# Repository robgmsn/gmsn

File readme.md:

Welcome to GMSN!

Your complete portal to building a DIY Open Source Synthesiser.

On the main [GMSN! Website](https://gmsn.co.uk/) you will find all the designs, PCBs and Panels, together with step by step instructions and parts lists.

Supporters of GMSN! can access build docs and support via the [GMSN! Forum](https://forum.gmsn.co.uk/). Please buy PCBs and Panels direct from the website to create a forum acccount.

This Github Repo contains the code for the digital modules. All of which are based on the ATMEGA328 microprocessor. This enable us to leverage the Arduino IDE and libraries, which speeds up code development and deployment.

You can also view the Eagle Schematics and Board files on [CADLAB.io](https://cadlab.io/project/24118). This displays component locations and also tracks changes between versions.

There's also the [GMSN! Youtube Channel](https://www.youtube.com/channel/UCwt7YFF0vUFElzAl-tT9rXA) for loads of great tips on getting started.

All designs are released under cc-by 4.0 license.

* SA - Share & Adapt.
* BY - Credit where credit is due.
* For any purpose including Commercial and Group Buys.
* No pressure to share design files

Time to build synths!

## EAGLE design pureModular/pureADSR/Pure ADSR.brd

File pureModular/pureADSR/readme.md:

DESIGN STATUS: Awaiting Testing - Ready for beta testing

ADSR Updated to V2.2 14/4/21

Library updated to include 3D models.
Traces rerouted.
DAC output filter remodelled.
Power replaced so 5V comes from power supply rather than 12V, in line with low noise techniques.

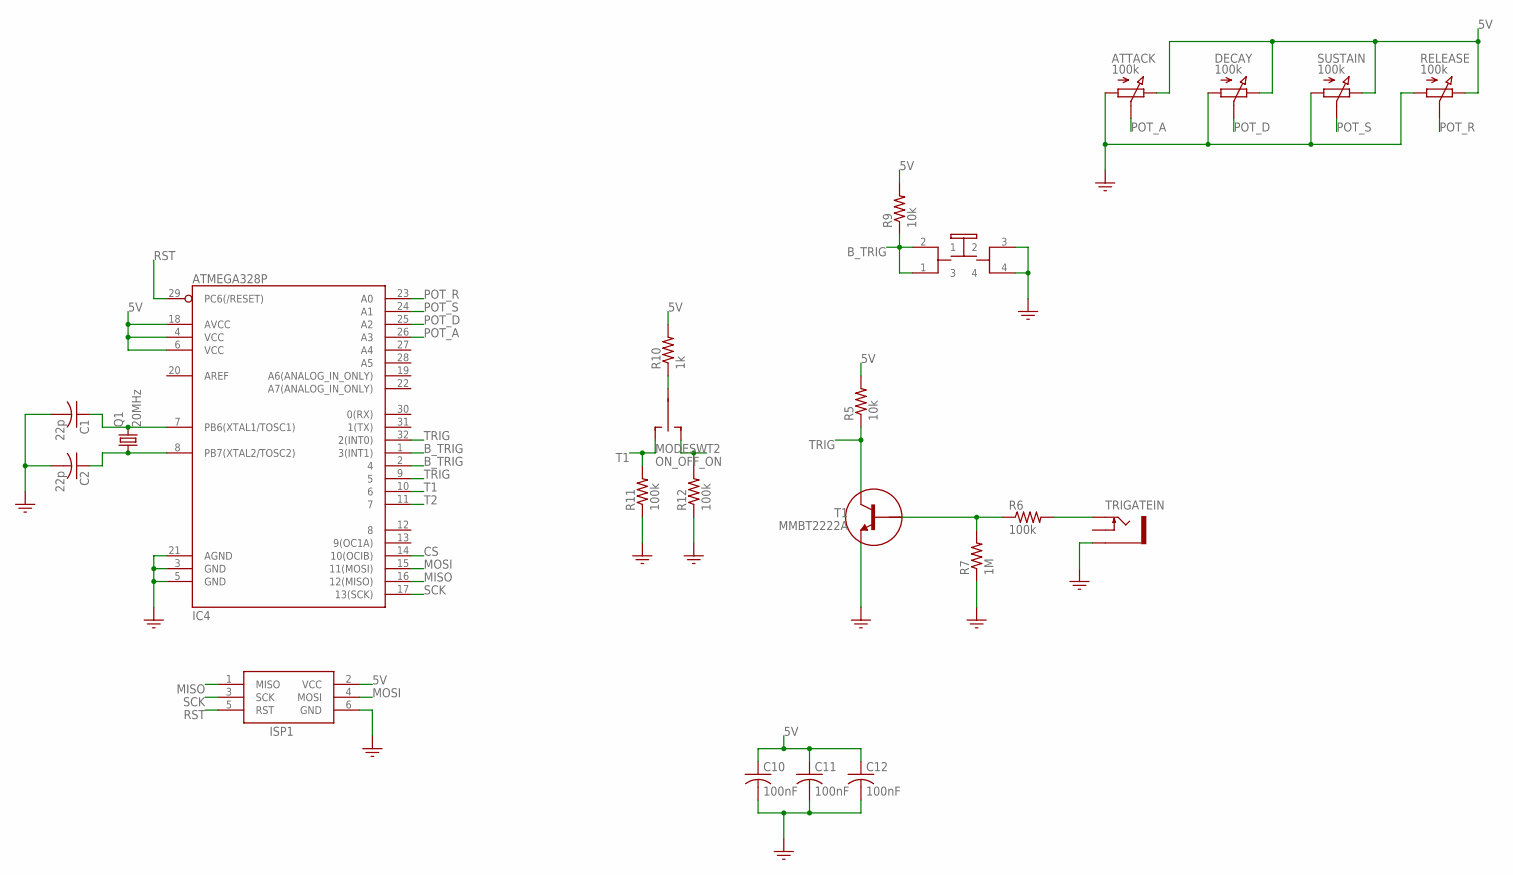
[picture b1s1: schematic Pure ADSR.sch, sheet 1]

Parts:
ATTACK: 100k; POTENTIOMETER_9MM
C1, C2: 22p; C0805
C10, C11, C12: 100nF; C0805
DECAY: 100k; POTENTIOMETER_9MM
IC4: ATMEGA328P; TQFP32-08
ISP1: HEADER2X3-6; AVRISP
MODESW: ON_OFF_ON; TOGGLE_SW
Q1: 20MHz; HC49UP
R5, R9: 10k; R0805
R6, R11, R12: 100k; R0805
R7: 1M; R0805
R10: 1k; R0805
RELEASE: 100k; POTENTIOMETER_9MM
SUSTAIN: 100k; POTENTIOMETER_9MM
T1: MMBT2222A; SOT23
TRIGATEIN: SOCKET_MONO_3.5MMPJ301M-12; PJ301M-12
TRIGGER: PB6149L-5; PB6149L

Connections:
5V: ATTACK.P$3 (3), C10.1, C11.1, C12.1, DECAY.P$3 (3), IC4.4 (VCC), IC4.6 (VCC), IC4.18 (AVCC), ISP1.2 (VCC), R5.2, R9.2, R10.2, RELEASE.P$3 (3), SUSTAIN.P$3 (3); also elsewhere on the board
B_TRIG: IC4.1 (3(INT1)), IC4.2 (4), R9.1, TRIGGER.1 (3), TRIGGER.2 (1)
CS: IC4.14 (10(OCIB)); also elsewhere on the board
GND: ATTACK.P$1 (1), C1.2, C2.2, C10.2, C11.2, C12.2, DECAY.P$1 (1), IC4.3 (GND), IC4.5 (GND), IC4.21 (AGND), ISP1.6 (GND), R7.1, R11.1, R12.1, RELEASE.P$1 (1), SUSTAIN.P$1 (1), T1.2 (E), TRIGATEIN.GND (SLEEVE), TRIGGER.3 (2), TRIGGER.4; also elsewhere on the board
MISO: IC4.16 (12(MISO)), ISP1.1 (MISO)
MOSI: IC4.15 (11(MOSI)), ISP1.4 (MOSI); also elsewhere on the board
unnamed: C1.1, IC4.7 (PB6(XTAL1/TOSC1)), Q1.2
unnamed: C2.1, IC4.8 (PB7(XTAL2/TOSC2)), Q1.1
unnamed: MODESW.2, R10.1
unnamed: R6.1, R7.2, T1.1 (B)
unnamed: R6.2, TRIGATEIN.TIP
POT_A: ATTACK.P$2 (2), IC4.26 (A3)
POT_D: DECAY.P$2 (2), IC4.25 (A2)
POT_R: IC4.23 (A0), RELEASE.P$2 (2)
POT_S: IC4.24 (A1), SUSTAIN.P$2 (2)
RST: IC4.29 (PC6(/RESET)), ISP1.5 (RST)
SCK: IC4.17 (13(SCK)), ISP1.3 (SCK); also elsewhere on the board
T1: IC4.10 (6), MODESW.3 (S), R11.2
T2: IC4.11 (7), MODESW.1 (O), R12.2
TRIG: IC4.9 (5), IC4.32 (2(INT0)), R5.1, T1.3 (C)

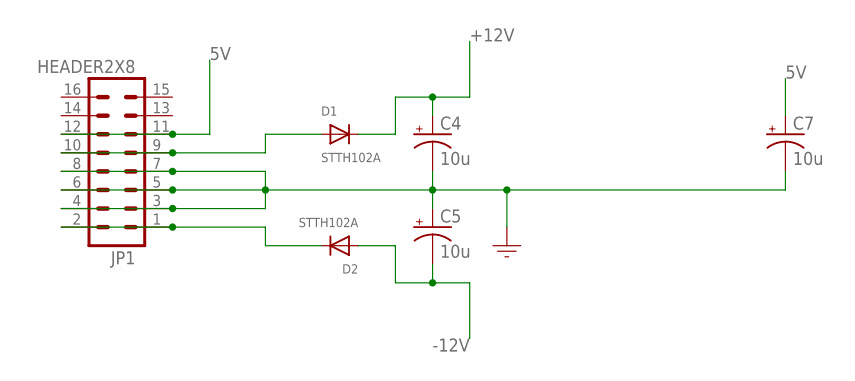
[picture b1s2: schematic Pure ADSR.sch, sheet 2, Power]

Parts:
C4, C5, C7: 10u; 153CLV-0505
D1, D2: STTH102A; SMADIODE
JP1: HEADER2X8; POWER_SHROUDED

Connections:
5V: C7.+, JP1.11, JP1.12; also elsewhere on the board
+12V: C4.+, D1.C; also elsewhere on the board
-12V: C5.-, D2.A; also elsewhere on the board
GND: C4.-, C5.+, C7.-, JP1.3, JP1.4, JP1.5, JP1.6, JP1.7, JP1.8; also elsewhere on the board
unnamed: D2.C, JP1.1, JP1.2
unnamed: D1.A, JP1.9, JP1.10

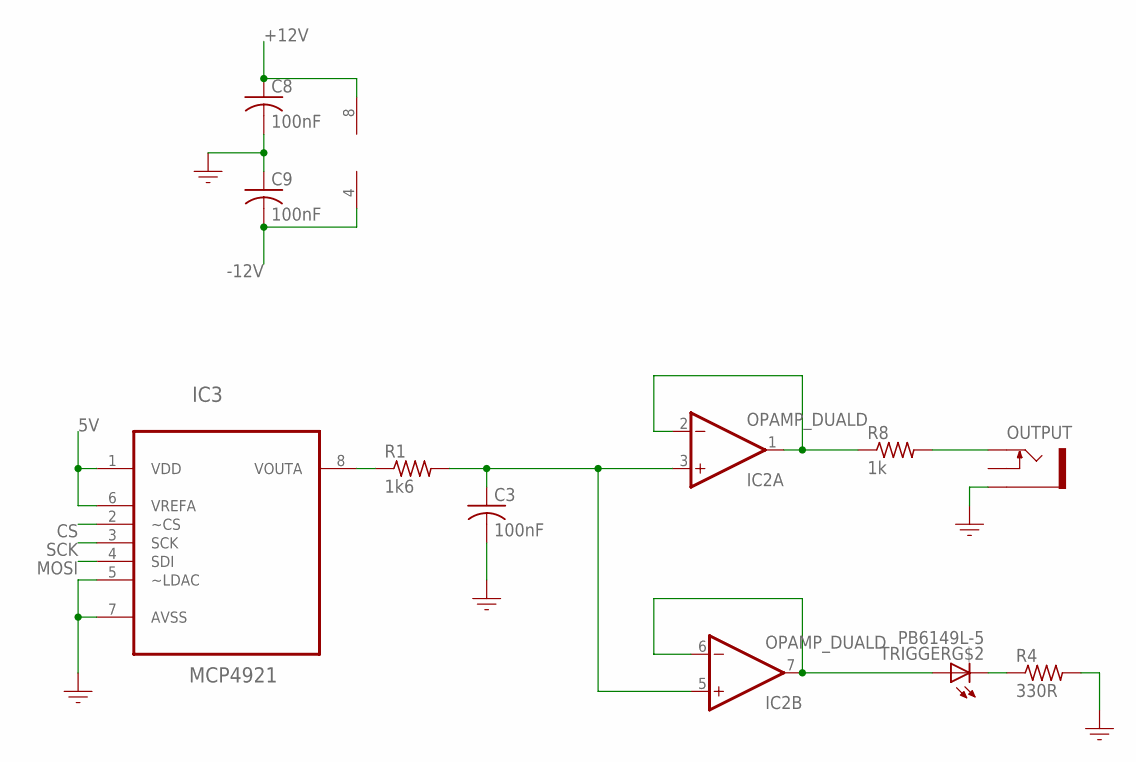
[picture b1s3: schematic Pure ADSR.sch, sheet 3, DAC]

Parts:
C3, C8, C9: 100nF; C0805
IC2: OPAMP_DUALD; SO08
IC3: MCP4921; SOIC8
OUTPUT: SOCKET_MONO_3.5MMPJ301M-12; PJ301M-12
R1: 1k6; R0805
R4: 330R; R0805
R8: 1k; R0805
TRIGGER: PB6149L-5; PB6149L

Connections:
5V: IC3.1 (VDD), IC3.6 (VREFA); also elsewhere on the board
+12V: C8.1, IC2.8 (V+); also elsewhere on the board
-12V: C9.2, IC2.4 (V-); also elsewhere on the board
CS: IC3.2 (~CS); also elsewhere on the board
GND: C3.2, C8.2, C9.1, IC3.5 (~LDAC), IC3.7 (AVSS), OUTPUT.GND (SLEEVE), R4.2; also elsewhere on the board
MOSI: IC3.4 (SDI); also elsewhere on the board
unnamed: IC3.8 (VOUTA), R1.1
unnamed: C3.1, IC2.3 (+IN), IC2.5 (+IN), R1.2
unnamed: IC2.1 (OUT), IC2.2 (-IN), R8.1
unnamed: IC2.6 (-IN), IC2.7 (OUT), TRIGGER.A
unnamed: R4.1, TRIGGER.K (C)
unnamed: OUTPUT.TIP, R8.2
SCK: IC3.3 (SCK); also elsewhere on the board

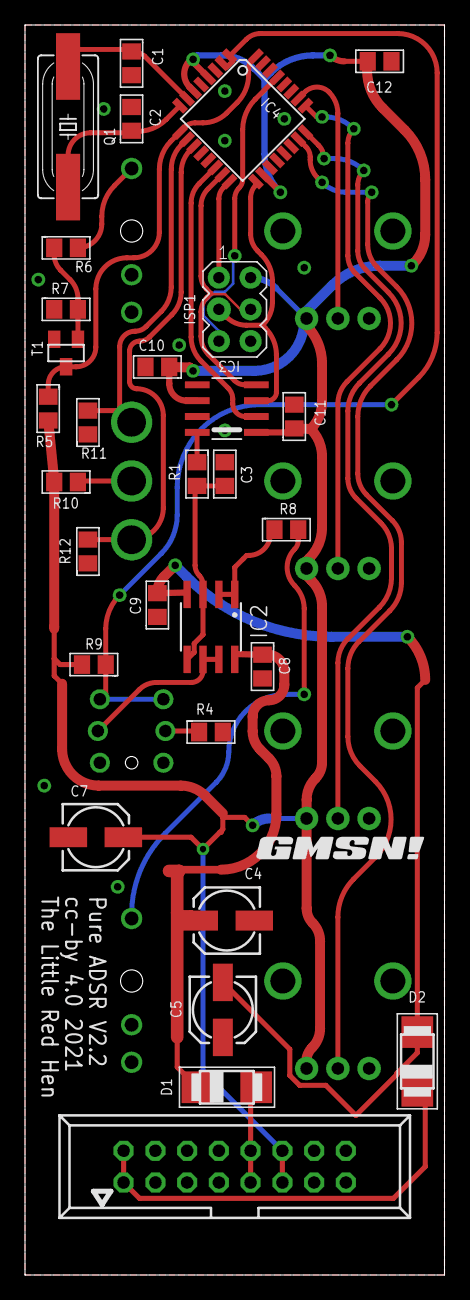
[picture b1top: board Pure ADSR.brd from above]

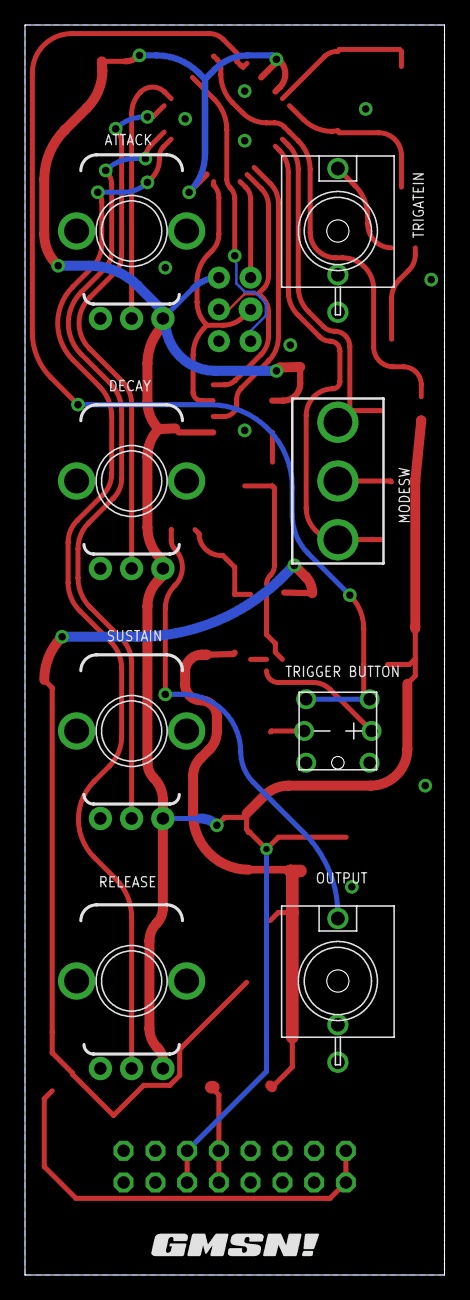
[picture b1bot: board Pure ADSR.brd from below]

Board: 2 copper layers, 33.6 x 100.0 mm, 40 parts (9 on the bottom side), 30 nets.

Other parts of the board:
U$1, U$2: GMSN!_LOGO

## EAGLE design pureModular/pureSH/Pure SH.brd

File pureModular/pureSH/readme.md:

DESIGN STATUS: Awaiting Testing - Ready for beta testing

S&H Updated to V1.5 14/4/21

Library updated to include 3D models.
Traces rerouted.

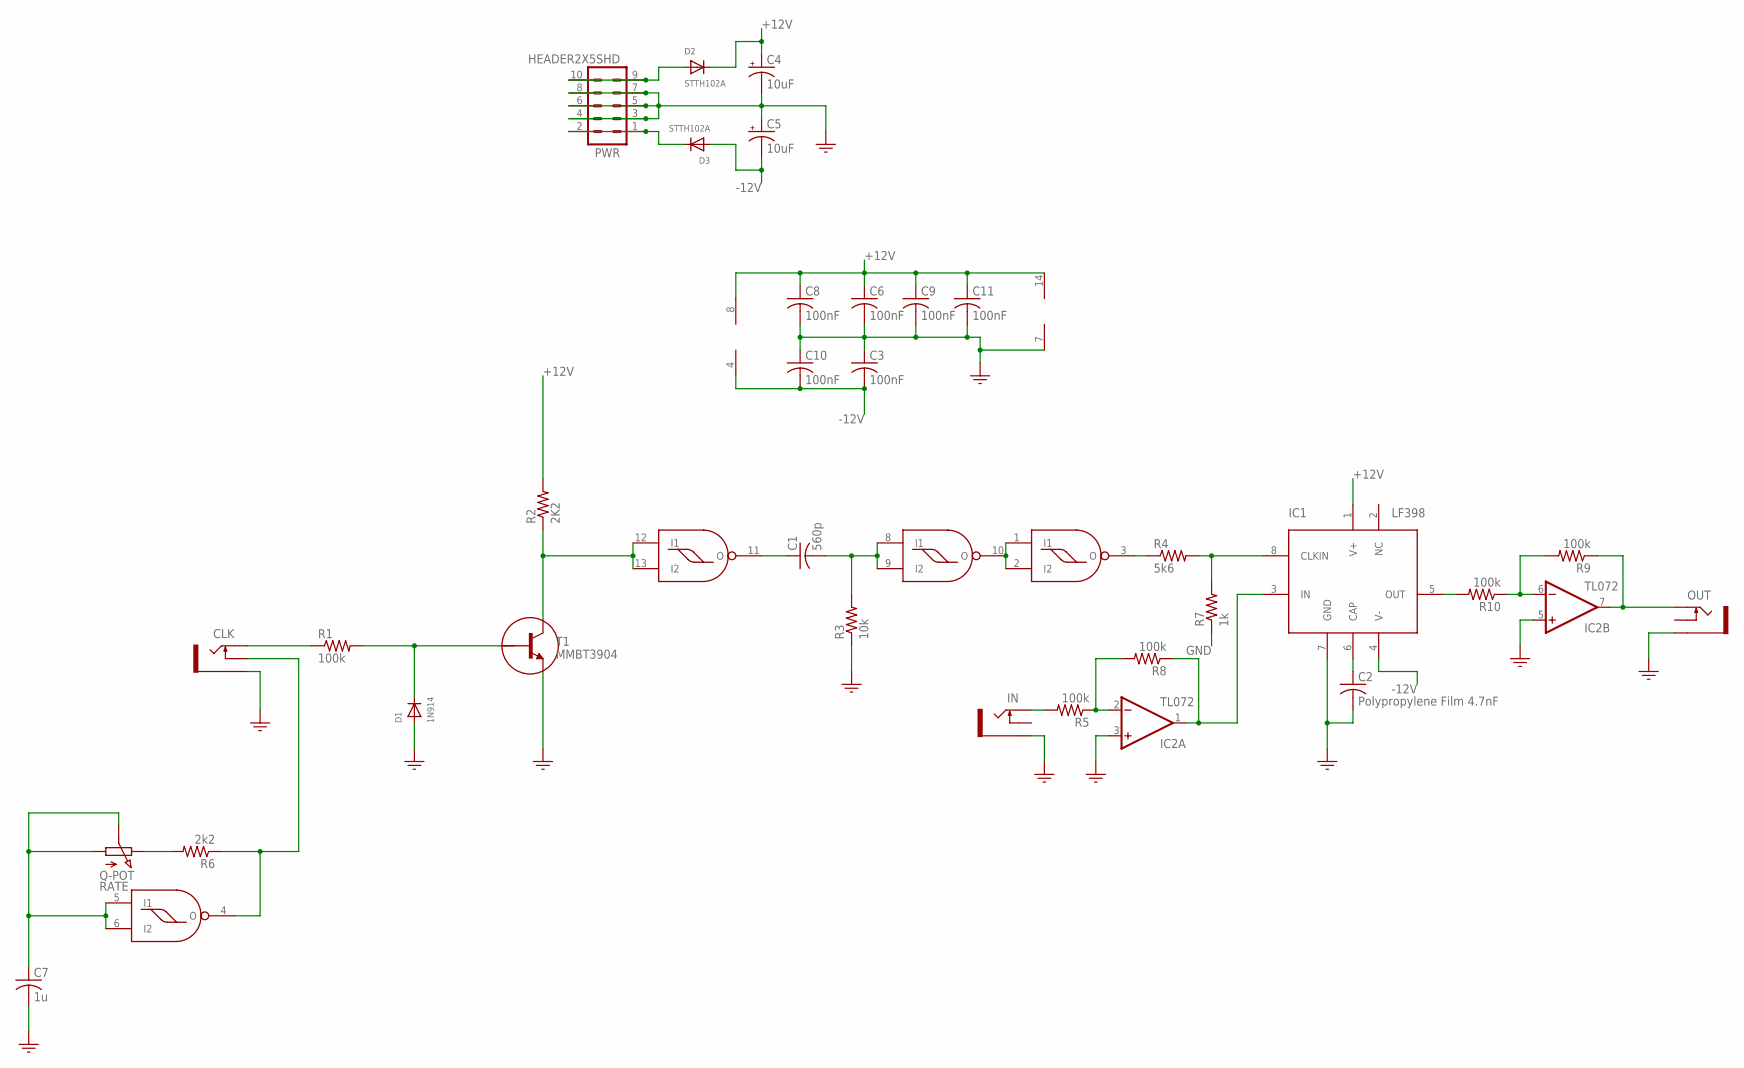
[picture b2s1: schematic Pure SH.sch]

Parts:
C1: 560p; C0805
C2: Polypropylene Film 4.7nF; C050-045X075
C3, C6, C8, C9, C10, C11: 100nF; C0805
C4, C5: 10uF; 153CLV-0505
C7: 1u; C0805
CLK: PJ301M-12
D1: 1N914; DO-41
D2, D3: STTH102A; SMADIODE
IC1: LF398; SOIC--8
IC2: TL072; SO08
IC3: cd4093; SOIC14
IN: PJ301M-12
OUT: PJ301M-12
PWR: HEADER2X5SHD; 2X5-SHROUDED
R1, R5, R8, R9, R10: 100k; R0805
R2: 2K2; R0805
R3: 10k; R0805
R4: 5k6; R0805
R6: 2k2; R0805
R7: 1k; R0805
RATE: Q-POT; POTENTIOMETER_9MM
T1: MMBT3904; SOT23

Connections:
+12V: C4.+, C6.1, C8.1, C9.1, C11.1, D2.C, IC1.1 (V+), IC2.8 (V+), IC3.14 (V+), R2.2
-12V: C3.2, C5.-, C10.2, D3.A, IC1.4 (V-), IC2.4 (V-)
GND: C2.2, C3.1, C4.-, C5.+, C6.2, C7.2, C8.2, C9.2, C10.1, C11.2, CLK.GND (SLEEVE), D1.A, IC1.7 (GND), IC2.3 (+IN), IC2.5 (+IN), IC3.7 (V-), IN.GND (SLEEVE), OUT.GND (SLEEVE), PWR.3, PWR.4, PWR.5, PWR.6, PWR.7, PWR.8, R3.1, R7.1, T1.2 (E)
unnamed: CLK.TIP, R1.1
unnamed: D1.C, R1.2, T1.1 (B)
unnamed: C1.1, IC3.11 (O)
unnamed: IC3.12 (I1), IC3.13 (I2), R2.1, T1.3 (C)
unnamed: IC3.1 (I1), IC3.2 (I2), IC3.10 (O)
unnamed: IC1.8 (CLKIN), R4.2, R7.2
unnamed: C1.2, IC3.8 (I1), IC3.9 (I2), R3.2
unnamed: IC3.3 (O), R4.1
unnamed: C2.1, IC1.6 (CAP)
unnamed: IN.TIP, R5.2
unnamed: IC2.2 (-IN), R5.1, R8.2
unnamed: R6.2, RATE.P$3 (3)
unnamed: C7.1, IC3.5 (I1), IC3.6 (I2), RATE.P$1 (1), RATE.P$2 (2)
unnamed: CLK.NORM (SWITCH), IC3.4 (O), R6.1
unnamed: IC1.3 (IN), IC2.1 (OUT), R8.1
unnamed: IC1.5 (OUT), R10.2
unnamed: IC2.6 (-IN), R9.2, R10.1
unnamed: IC2.7 (OUT), OUT.TIP, R9.1
unnamed: D2.A, PWR.9, PWR.10
unnamed: D3.C, PWR.1, PWR.2

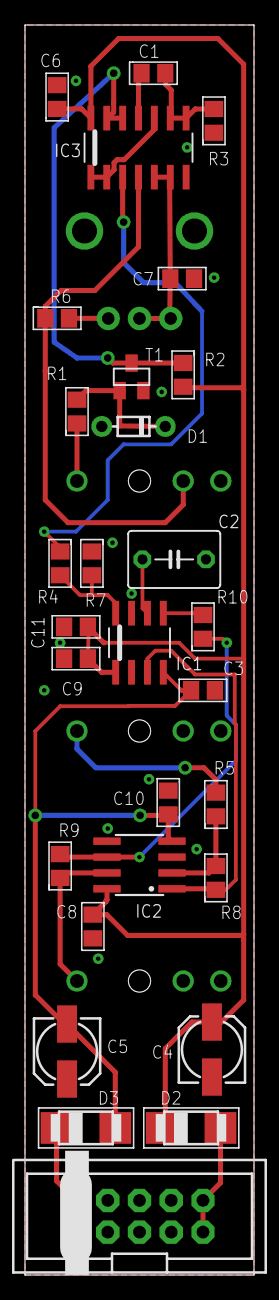
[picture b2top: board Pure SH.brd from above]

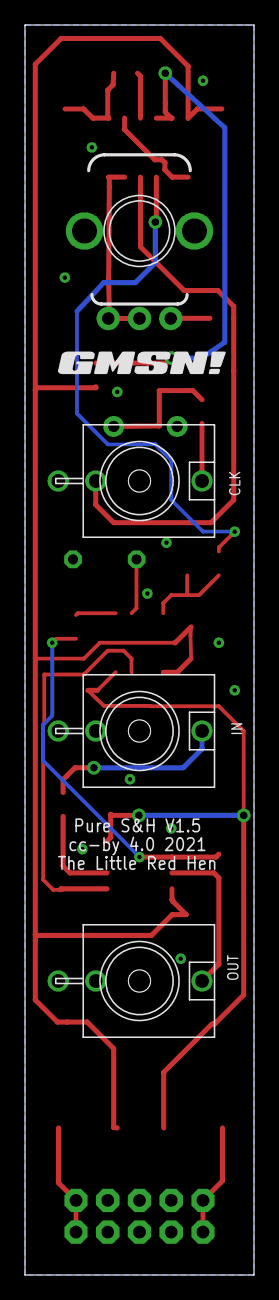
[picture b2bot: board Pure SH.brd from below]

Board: 2 copper layers, 18.3 x 100.0 mm, 34 parts (5 on the bottom side), 23 nets.

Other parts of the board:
U$3: GMSN!_LOGO

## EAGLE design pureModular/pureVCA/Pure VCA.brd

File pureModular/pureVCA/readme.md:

DESIGN STATUS: Awaiting Testing - Ready for beta testing

VCA Updated to V2.3 14/4/21

Library updated to include 3D models.
Traces rerouted.
Weird shorted cap removed. WTF?

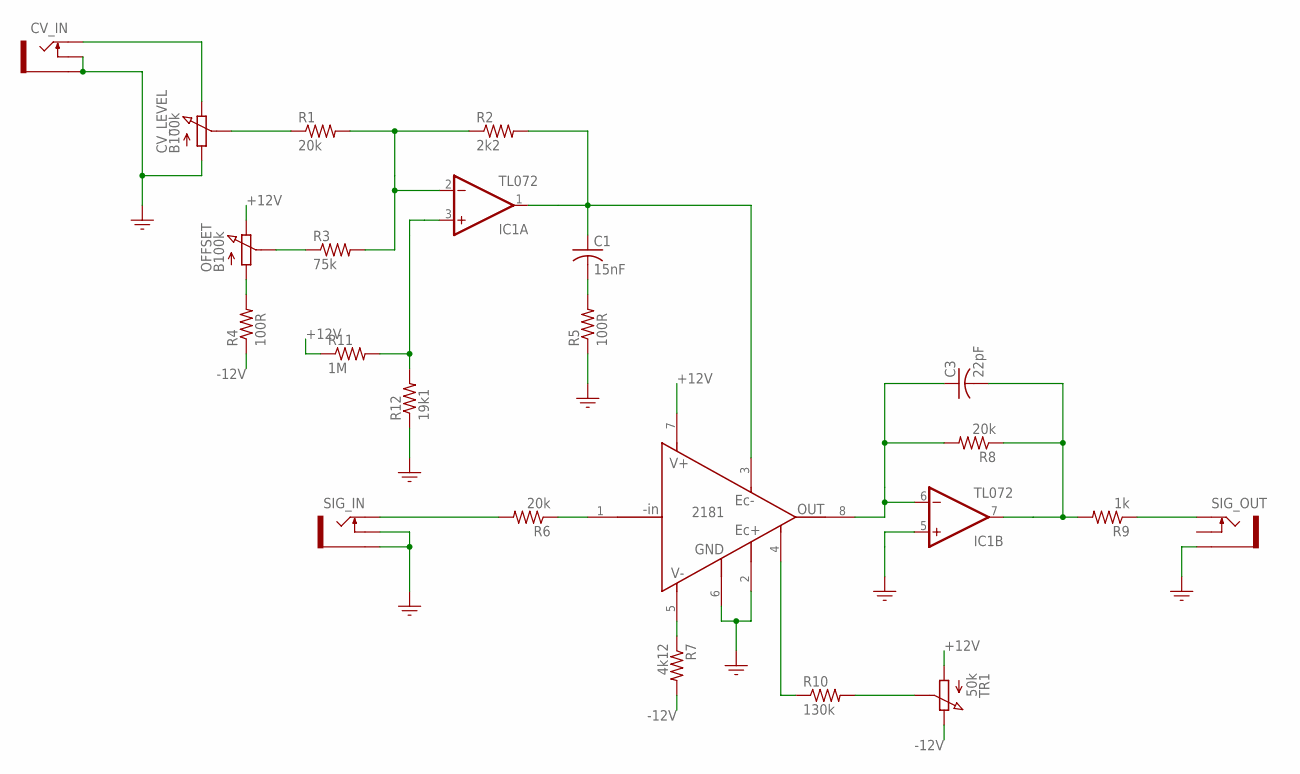
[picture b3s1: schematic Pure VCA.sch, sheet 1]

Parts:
C1: 15nF; C0805
C3: 22pF; C0805
CV_IN: PJ301M-12
CV_LEVEL: B100k; POT_9MM_GREEN_KNOB
IC1: TL072; SO08
IC2: THAT2181; SOIC--8
OFFSET: B100k; POT_9MM_BLUE_KNOB
R1, R6, R8: 20k; R0805
R2: 2k2; R0805
R3: 75k; R0805
R4, R5: 100R; R0805
R7: 4k12; R0805
R9: 1k; R0805
R10: 130k; R0805
R11: 1M; R0805
R12: 19k1; R0805
SIG_IN: PJ301M-12
SIG_OUT: PJ301M-12
TR1: 50k; TRIMMER_TH

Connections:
+12V: IC2.7 (V+), OFFSET.P$3 (3), R11.1, TR1.1; also elsewhere on the board
-12V: R4.1, R7.2, TR1.3; also elsewhere on the board
GND: CV_IN.GND (SLEEVE), CV_IN.NORM (SWITCH), CV_LEVEL.P$1 (1), IC1.5 (+IN), IC2.2 (EC+), IC2.6 (GND), R5.1, R12.1, SIG_IN.GND (SLEEVE), SIG_IN.NORM (SWITCH), SIG_OUT.GND (SLEEVE); also elsewhere on the board
unnamed: CV_IN.TIP, CV_LEVEL.P$3 (3)
unnamed: IC1.2 (-IN), R1.2, R2.1, R3.2
unnamed: CV_LEVEL.P$2 (2), R1.1
unnamed: OFFSET.P$1 (1), R4.2
unnamed: C1.1, IC1.1 (OUT), IC2.3 (EC-), R2.2
unnamed: OFFSET.P$2 (2), R3.1
unnamed: C1.2, R5.2
unnamed: R9.1, SIG_OUT.TIP
unnamed: IC2.1 (-IN), R6.1
unnamed: R6.2, SIG_IN.TIP
unnamed: IC2.5 (V-), R7.1
unnamed: IC1.3 (+IN), R11.2, R12.2
unnamed: C3.1, IC1.6 (-IN), IC2.8 (OUT), R8.2
unnamed: C3.2, IC1.7 (OUT), R8.1, R9.2
unnamed: IC2.4 (SYM), R10.1
unnamed: R10.2, TR1.2

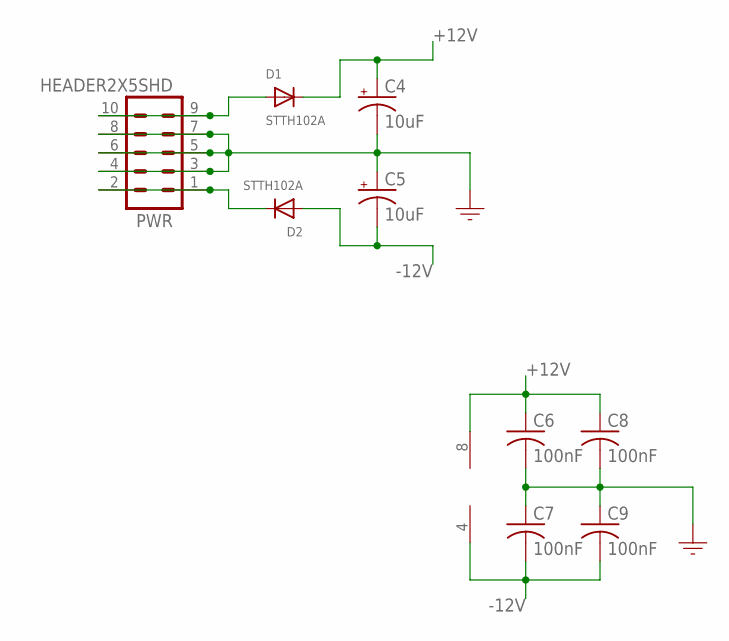
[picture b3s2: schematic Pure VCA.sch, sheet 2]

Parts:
C4, C5: 10uF; 153CLV-0505
C6, C7, C8, C9: 100nF; C0805
D1, D2: STTH102A; SMADIODE
IC1: TL072; SO08
PWR: HEADER2X5SHD; 2X5-SHROUDED

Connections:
+12V: C4.+, C6.1, C8.1, D1.C, IC1.8 (V+); also elsewhere on the board
-12V: C5.-, C7.2, C9.2, D2.A, IC1.4 (V-); also elsewhere on the board
GND: C4.-, C5.+, C6.2, C7.1, C8.2, C9.1, PWR.3, PWR.4, PWR.5, PWR.6, PWR.7, PWR.8; also elsewhere on the board
unnamed: D1.A, PWR.9, PWR.10
unnamed: D2.C, PWR.1, PWR.2

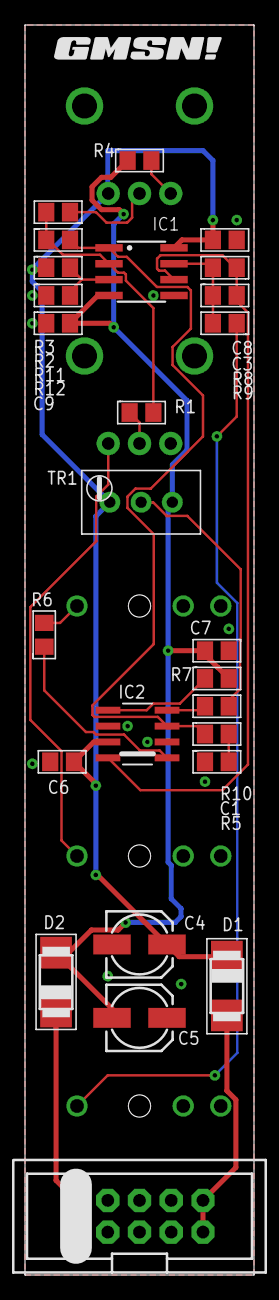
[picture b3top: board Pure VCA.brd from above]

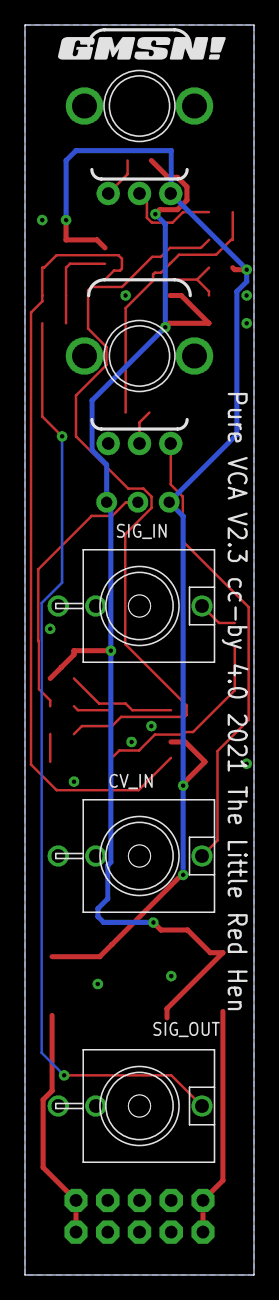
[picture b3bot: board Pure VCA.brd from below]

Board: 2 copper layers, 18.3 x 100.0 mm, 33 parts (6 on the bottom side), 21 nets.

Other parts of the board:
U$1, U$2: GMSN!_LOGO

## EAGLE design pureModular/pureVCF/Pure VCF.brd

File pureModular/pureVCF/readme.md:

DESIGN STATUS: Awaiting Testing - Not for public consumption.

VCF Updated to V2.5 14/04/21

Library updated to 3D models.
Changed the CV mixer from Average to Sum and added inverter stage to retain consistency.
Some resistor values reduced to 10K, inline with low noise techniques.
Rerouted and reduced some traces.

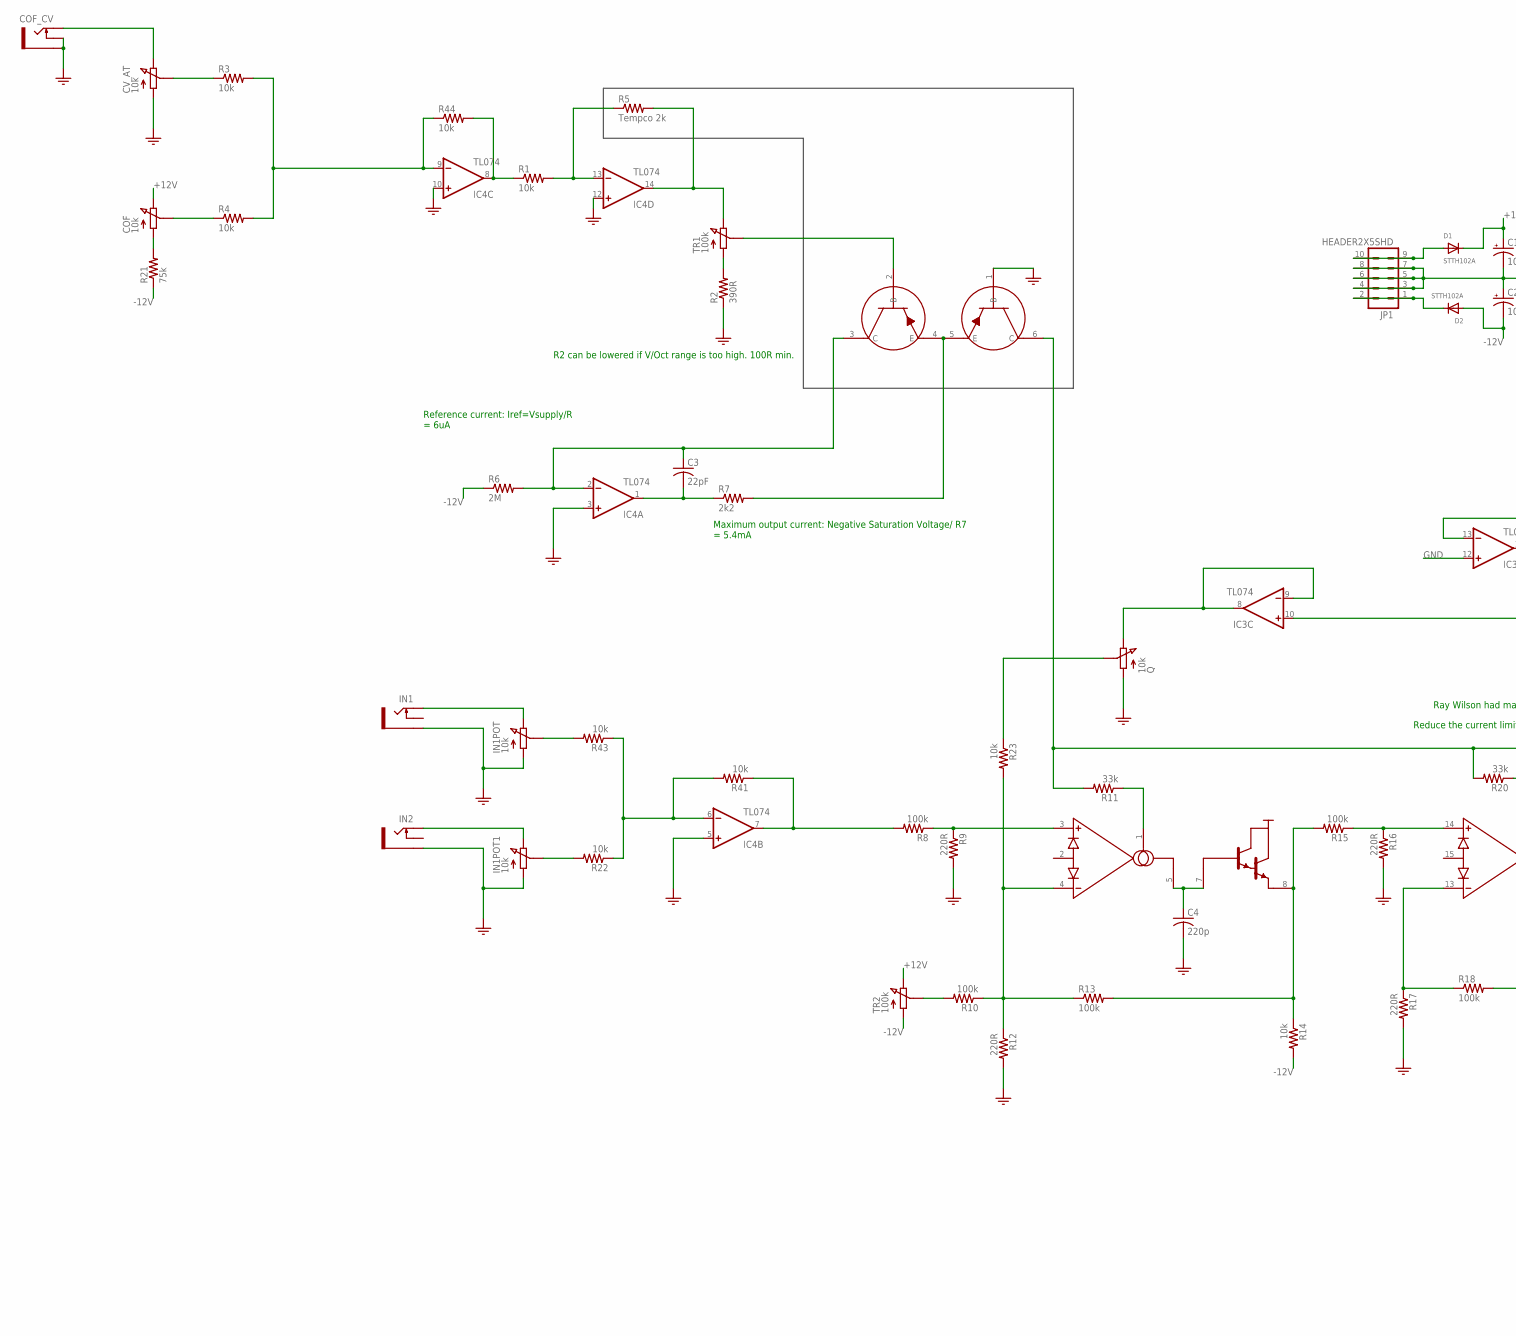
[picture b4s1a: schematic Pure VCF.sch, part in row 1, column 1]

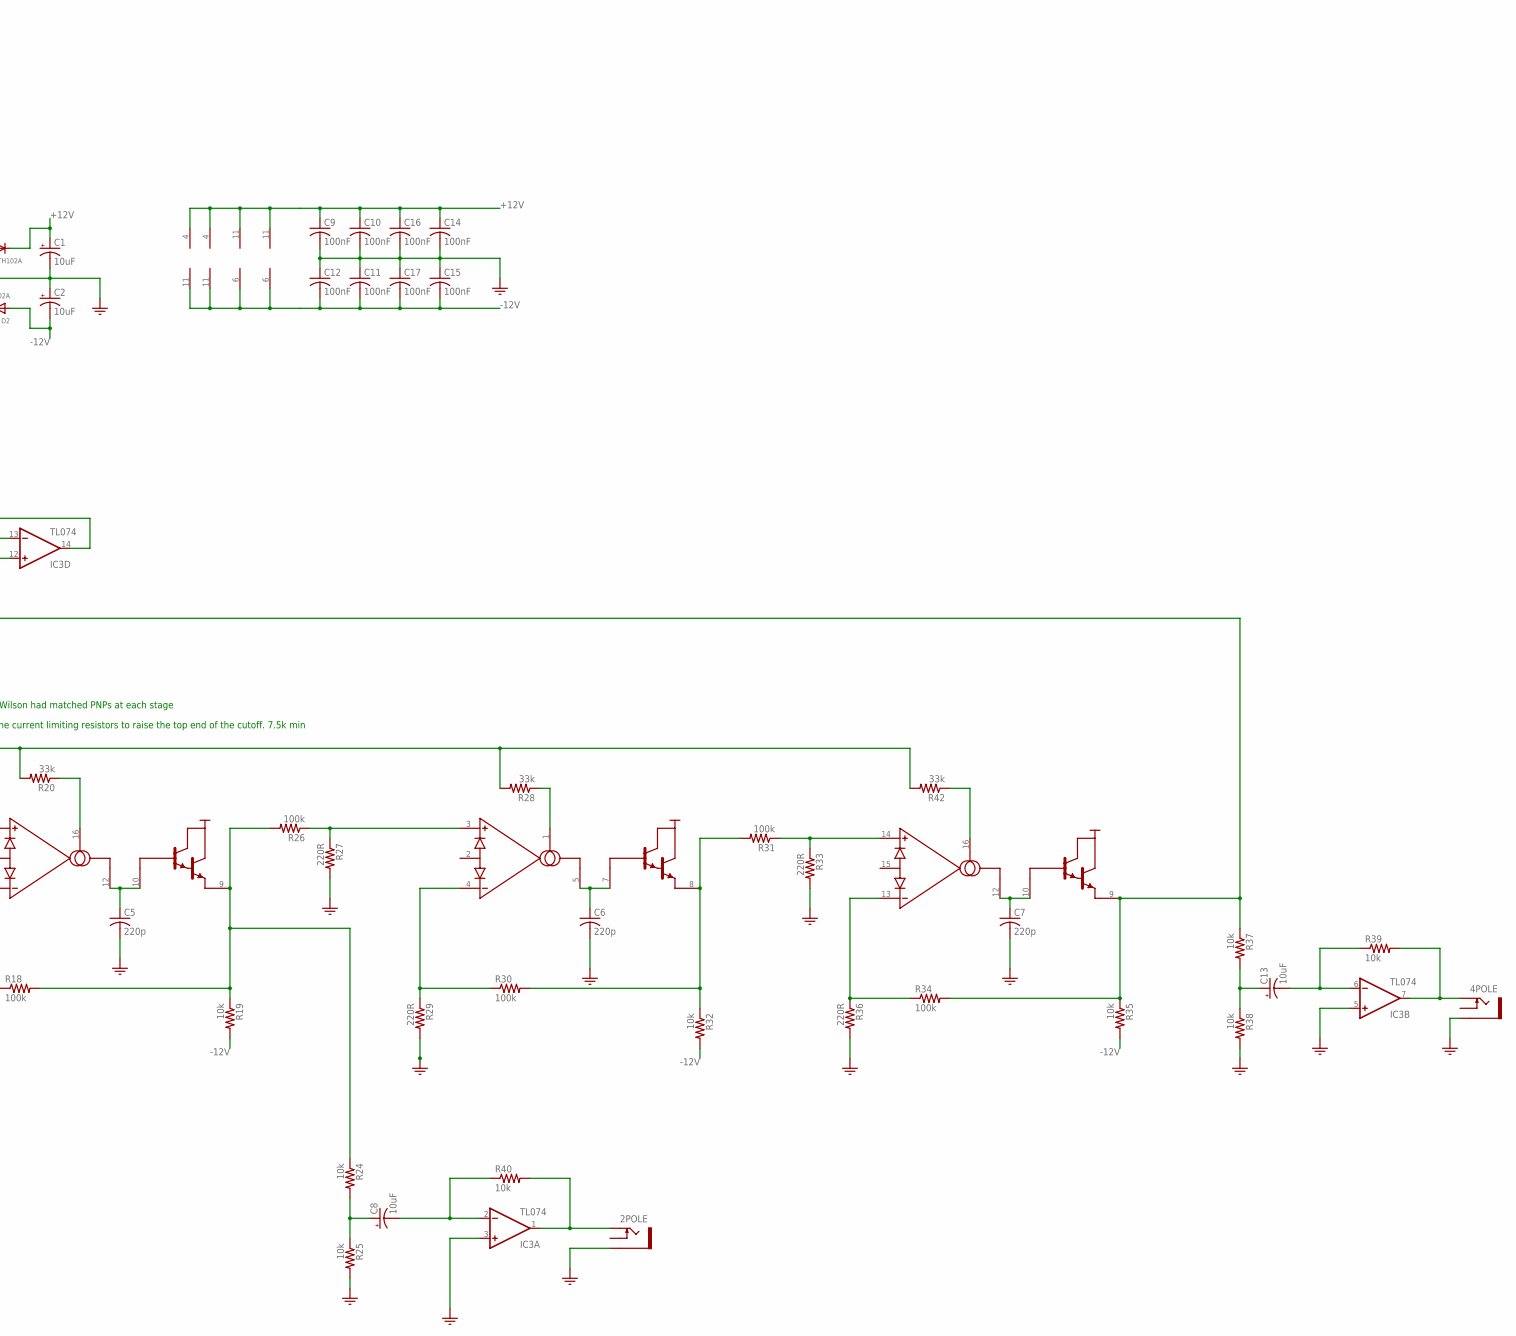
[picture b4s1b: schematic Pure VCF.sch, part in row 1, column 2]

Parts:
2POLE, 4POLE: PJ301M-12
C1, C2, C8, C13: 10uF; 153CLV-0505
C3: 22pF; C0805
C4, C5, C6, C7: 220p; C050-045X075
C9, C10, C11, C12, C14, C15, C16, C17: 100nF; C0805
COF: 10k; POT_9MM_RED_KNOB
COF_CV: PJ301M-12
CV_AT: 10k; POT_9MM_GREEN_KNOB
D1, D2: STTH102A; SMADIODE
IC1, IC2: LM13700; SOIC-16_BLANK
IC3, IC4: TL074; SO14
IN1, IN2: PJ301M-12
IN1POT, IN1POT1: 10k; POT_9MM_BLUE_KNOB
JP1: HEADER2X5SHD; 2X5-SHROUDED
Q: 10k; POT_9MM_YELLOW_KNOB
R1, R3, R4, R14, R19, R22, R23, R24, R25, R32, R35, R37, R38, R39, R40, R41, R43, R44: 10k; R0805
R2: 390R; R0805
R5: Tempco 2k; 0207/8.5
R6: 2M; R0805
R7: 2k2; R0805
R8, R10, R13, R15, R18, R26, R30, R31, R34: 100k; R0805
R9, R12, R16, R17, R27, R29, R33, R36: 220R; R0805
R11, R20, R28, R42: 33k; R0805
R21: 75k; R0805
T1: DMMT3906W; TRANS_PAIR
TR1, TR2: 100k; TRIMMER_TH

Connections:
+12V: C1.+, C9.1, C10.1, C14.1, C16.1, COF.P$3 (3), D1.C, IC1.11 (V+), IC2.11 (V+), IC3.4 (V+), IC4.4 (V+), TR2.3
-12V: C2.-, C11.2, C12.2, C15.2, C17.2, D2.A, IC1.6 (V-), IC2.6 (V-), IC3.11 (V-), IC4.11 (V-), R6.1, R14.2, R19.2, R21.1, R32.2, R35.2, TR2.1
GND: 2POLE.GND (SLEEVE), 4POLE.GND (SLEEVE), C1.-, C2.+, C4.2, C5.2, C6.2, C7.2, C9.2, C10.2, C11.1, C12.1, C14.2, C15.1, C16.2, C17.1, COF_CV.GND (SLEEVE), COF_CV.NORM (SWITCH), CV_AT.P$1 (1), IC3.3 (+IN), IC3.5 (+IN), IC3.12 (+IN), IC4.3 (+IN), IC4.5 (+IN), IC4.10 (+IN), IC4.12 (+IN), IN1.GND (SLEEVE), IN1POT.P$1 (1), IN1POT1.P$1 (1), IN2.GND (SLEEVE), JP1.3, JP1.4, JP1.5, JP1.6, JP1.7, JP1.8, Q.P$1 (1), R2.1, R9.2, R12.2, R16.2, R17.2, R25.2, R27.2, R29.2, R33.2, R36.2, R38.2, T1.1 (B)
unnamed: C5.1, IC1.10 (BUF-IN_2), IC1.12 (OUT)
unnamed: T1.2 (B), TR1.2
unnamed: R2.2, TR1.1
unnamed: IC1.4 (IN-), R10.1, R12.1, R13.1, R23.2
unnamed: IC4.14 (OUT), R5.2, TR1.3
unnamed: IC4.13 (-IN), R1.2, R5.1
unnamed: COF_CV.TIP, CV_AT.P$3 (3)
unnamed: CV_AT.P$2 (2), R3.1
unnamed: COF.P$2 (2), R4.1
unnamed: C3.1, IC4.2 (-IN), R6.2, T1.3 (C)
unnamed: C3.2, IC4.1 (OUT), R7.1
unnamed: IC1.1 (BIAS-IN), R11.1
unnamed: R7.2, T1.4 (E), T1.5 (E)
unnamed: IC4.6 (-IN), R22.1, R41.2, R43.1
unnamed: IC1.9 (BUF-OUT_2), R18.2, R19.1, R24.1, R26.2
unnamed: IC1.3 (IN+), R8.1, R9.1
unnamed: C8.-, IC3.2 (-IN), R40.1
unnamed: Q.P$2 (2), R23.1
unnamed: IC3.8 (OUT), IC3.9 (-IN), Q.P$3 (3)
unnamed: C13.-, IC3.6 (-IN), R39.1
unnamed: IC1.16 (BIAS-IN), R20.1
unnamed: IC1.14 (IN+), R15.1, R16.1
unnamed: IC1.13 (IN-), R17.1, R18.1
unnamed: COF.P$1 (1), R21.2
unnamed: C8.+, R24.2, R25.1
unnamed: C4.1, IC1.5 (OUT), IC1.7 (BUF-IN_2)
unnamed: IC1.8 (BUF-OUT_2), R13.2, R14.1, R15.2
unnamed: IC2.3 (IN+), R26.1, R27.1
unnamed: 2POLE.TIP, IC3.1 (OUT), R40.2
unnamed: IC2.16 (BIAS-IN), R42.1
unnamed: IC4.7 (OUT), R8.2, R41.1
unnamed: IC2.4 (IN-), R29.1, R30.1
unnamed: IC4.8 (OUT), R1.1, R44.2
unnamed: R11.2, R20.2, R28.2, R42.2, T1.6 (C)
unnamed: C13.+, R37.2, R38.1
unnamed: IC3.13 (-IN), IC3.14 (OUT)
unnamed: D1.A, JP1.9, JP1.10
unnamed: IC4.9 (-IN), R3.2, R4.2, R44.1
unnamed: IC2.13 (IN-), R34.1, R36.1
unnamed: 4POLE.TIP, IC3.7 (OUT), R39.2
unnamed: IC2.14 (IN+), R31.1, R33.1
unnamed: IC2.8 (BUF-OUT_2), R30.2, R31.2, R32.1
unnamed: IC2.9 (BUF-OUT_2), IC3.10 (+IN), R34.2, R35.1, R37.1
unnamed: IN1.TIP, IN1POT.P$3 (3)
unnamed: IN1POT1.P$3 (3), IN2.TIP
unnamed: D2.C, JP1.1, JP1.2
unnamed: IN1POT.P$2 (2), R43.2
unnamed: R10.2, TR2.2
unnamed: IN1POT1.P$2 (2), R22.2
unnamed: C6.1, IC2.5 (OUT), IC2.7 (BUF-IN_2)
unnamed: C7.1, IC2.10 (BUF-IN_2), IC2.12 (OUT)
unnamed: IC2.1 (BIAS-IN), R28.1

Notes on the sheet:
Reference current: Iref=Vsupply/R = 6uA
Maximum output current: Negative Saturation Voltage/ R7 = 5.4mA
R2 can be lowered if V/Oct range is too high. 100R min.
Reduce the current limiting resistors to raise the top end of the cutoff. 7.5k min
Ray Wilson had matched PNPs at each stage

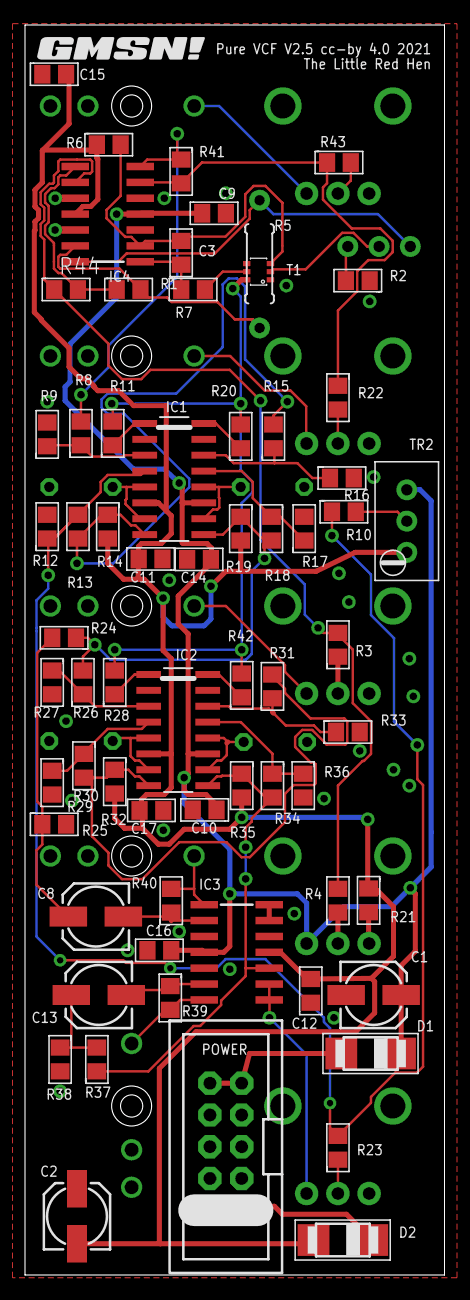
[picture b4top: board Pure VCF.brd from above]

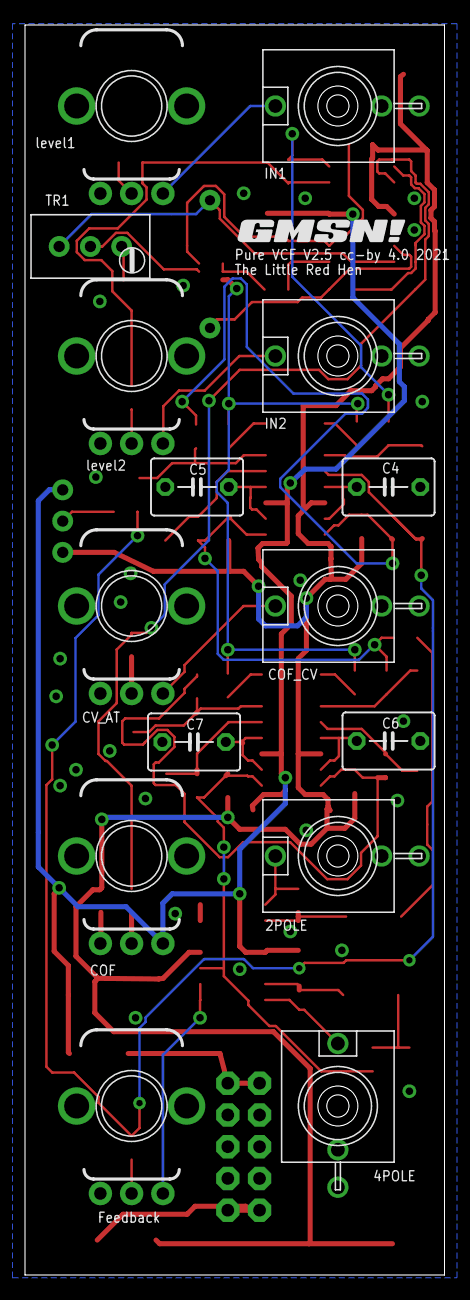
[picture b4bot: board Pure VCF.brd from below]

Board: 2 copper layers, 33.6 x 100.0 mm, 83 parts (16 on the bottom side), 55 nets.

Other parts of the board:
U$1, U$2: GMSN!_LOGO

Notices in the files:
pureModular/pureADSR/Pure ADSR.brd:
cc-by 4.0 2021
pureModular/pureDigit/Pure Digit.brd:
cc-by 0.5
pureModular/purePowerStrip/Pure Power Strip.brd:
Pure Power Strip v1 cc-by 4.0
pureModular/pureVCA/Pure VCA.brd:
Pure VCA V2.3 cc-by 4.0 2021 The Little Red Hen
pureModular/pureVCF/Pure VCF.brd:
Pure VCF V2.5 cc-by 4.0 2021
pureModular/pureVCO/Pure VCO.brd:
Pure VCO V3.1 cc-by 4.0 2021
